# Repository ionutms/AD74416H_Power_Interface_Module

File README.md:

# AD74416H Power Interface Module

## Overview

This repository provides a comprehensive KiCad design for a power and interface module tailored for the Analog Devices AD74416H. This module is designed to supply the necessary power rails and handle digital communications, making it an essential companion for projects utilizing the [Minimal_AD74416H](https://github.com/ionutms/Minimal_AD74416H) board or other AD74416H-based systems.

## Disclaimer

> [!NOTE]
> This project is provided "as is" and without any warranty, express or implied. For more details, please see the [LICENSE](LICENSE) file.

## About the Module

The AD74416H Power Interface Module is engineered to simplify the integration of the AD74416H by providing a stable and reliable power source and a straightforward digital interface. It takes a single power input and generates all the required voltage levels for the AD74416H and its peripherals.

Key features of this module include:

- **Power Supply Generation:** Onboard regulators to generate the necessary positive and negative supply rails for the AD74416H.
- **Digital Interface:** Provides a clear and accessible interface for SPI communication and other digital signals.
- **Modular Design:** Designed to seamlessly connect with the Minimal_AD74416H board.
- **User-Friendly Connectors:** Equipped with standard connectors for easy integration into larger systems.

## Project Structure

```
ad74416h_power_interface_module/
├── ad74416h_power_interface_module.kicad_pro               # Project configuration file
├── ad74416h_power_interface_module.kicad_sch               # Main schematic file
├── ad74416h_power_interface_module.kicad_pcb               # PCB layout file
├── fp-lib-table                                            # Footprint library table
├── sym-lib-table                                           # Symbol library table
├── docs/                                                   # Documentation files
│   ├── bom/                                                # Bill of Materials
│   │   └── ad74416h_power_interface_module_ibom.html       # Interactive BOM file
│   ├── pictures/                                           # Images and photos
│   │   ├── 1_ad74416h_power_interface_module_side.png      # Side view of PCB
│   │   ├── 2_ad74416h_power_interface_module_top.png       # Top view of PCB
│   │   └── 3_ad74416h_power_interface_module_bottom.png    # Bottom view of PCB
│   └── schematics/                                         # Schematic PDF exports
│       └── ad74416h_power_interface_module_schematics.pdf  # Complete schematics PDF
└── KiCAD_Symbols_Generator/                                # Submodule for symbol generation from CSV data
```

## Project Features

This design provides a robust power and interface solution for the AD74416H with:

-   Efficient power conversion and regulation
-   Clear separation of analog and digital grounds
-   Easy-to-use connectors for power and data
-   A compact and modular PCB design

## Getting Started

### Prerequisites

-   [KiCad EDA](https://www.kicad.org/) version 9.0 or later installed on your system
-   Git (for cloning the repository and submodule management)

### Opening the Project

1.  **Clone the repository** (including submodules):
    ```bash
    git clone --recursive https://github.com/ionutms/AD74416H_Power_Interface_Module.git
    ```

    If you've already cloned the repository without submodules, initialize them with:
    ```bash
    git submodule init
    git submodule update
    ```

2.  **Open the project in KiCad**:
    -   Launch KiCad
    -   Click "Open Existing Project"
    -   Navigate to the cloned repository folder
    -   Select the `ad74416h_power_interface_module.kicad_pro` file

3.  **Explore the design**:
    -   Open the schematic editor to view the circuit design
    -   Open the PCB editor to view the board layout
    -   Review the symbol and footprint libraries used in the design

### Project Files

-   **Main schematic**: `ad74416h_power_interface_module.kicad_sch` - Contains the primary circuit design for the power supply and digital interface.
-   **PCB layout**: `ad74416h_power_interface_module.kicad_pcb` - Physical board design file.
-   **Project configuration**: `ad74416h_power_interface_module.kicad_pro` - KiCad project settings.

## Dependencies

This project has the following dependencies:

### 1. KiCAD Symbols Generator

This repository uses [KiCAD_Symbols_Generator](https://github.com/ionutms/KiCAD_Symbols_Generator) as a submodule for custom symbol generation.

To initialize the submodule after cloning this repository:

```bash
git submodule update --init --recursive
```

### 2. 3D Models

This project requires the [3D_Models_Vault](https://github.com/ionutms/3D_Models_Vault) repository for 3D models.

#### Setup for KiCAD 9:

1.  Clone the 3D models repository:
    ```bash
    git clone https://github.com/ionutms/3D_Models_Vault.git
    ```

2.  In KiCAD 9, add an environment variable:
    -   Variable name: `KICAD9_3D_MODELS_VAULT`
    -   Variable value: Full path to where you cloned the 3D_Models_Vault repository

## Usage

After setting up the dependencies, open the project in KiCad 9 to access all features including the 3D models. This module can be used to power and communicate with the [Minimal_AD74416H](https://github.com/ionutms/Minimal_AD74416H) board.

## Symbol Generator Submodule

This project includes the KiCAD_Symbols_Generator as a submodule, which provides tools for generating KiCad symbols from CSV data files. For more information on using this tool, see the [KiCAD_Symbols_Generator documentation](ad74416h_power_interface_module/KiCAD_Symbols_Generator/README.md).

## Documentation

The `docs` folder contains:
-   Schematic PDF exports
-   Images and photos of the design

## Visuals

The following images showcase the PCB design from different perspectives:

*Top View of the PCB*

*Side View of the PCB*

*Bottom View of the PCB*

## License

This project is licensed under the MIT License - see the [LICENSE](LICENSE) file for details.

## References

-   [AD74416H Datasheet](https://www.analog.com/media/en/technical-documentation/data-sheets/ad74416h.pdf)
-   [KiCad EDA](https://www.kicad.org/)

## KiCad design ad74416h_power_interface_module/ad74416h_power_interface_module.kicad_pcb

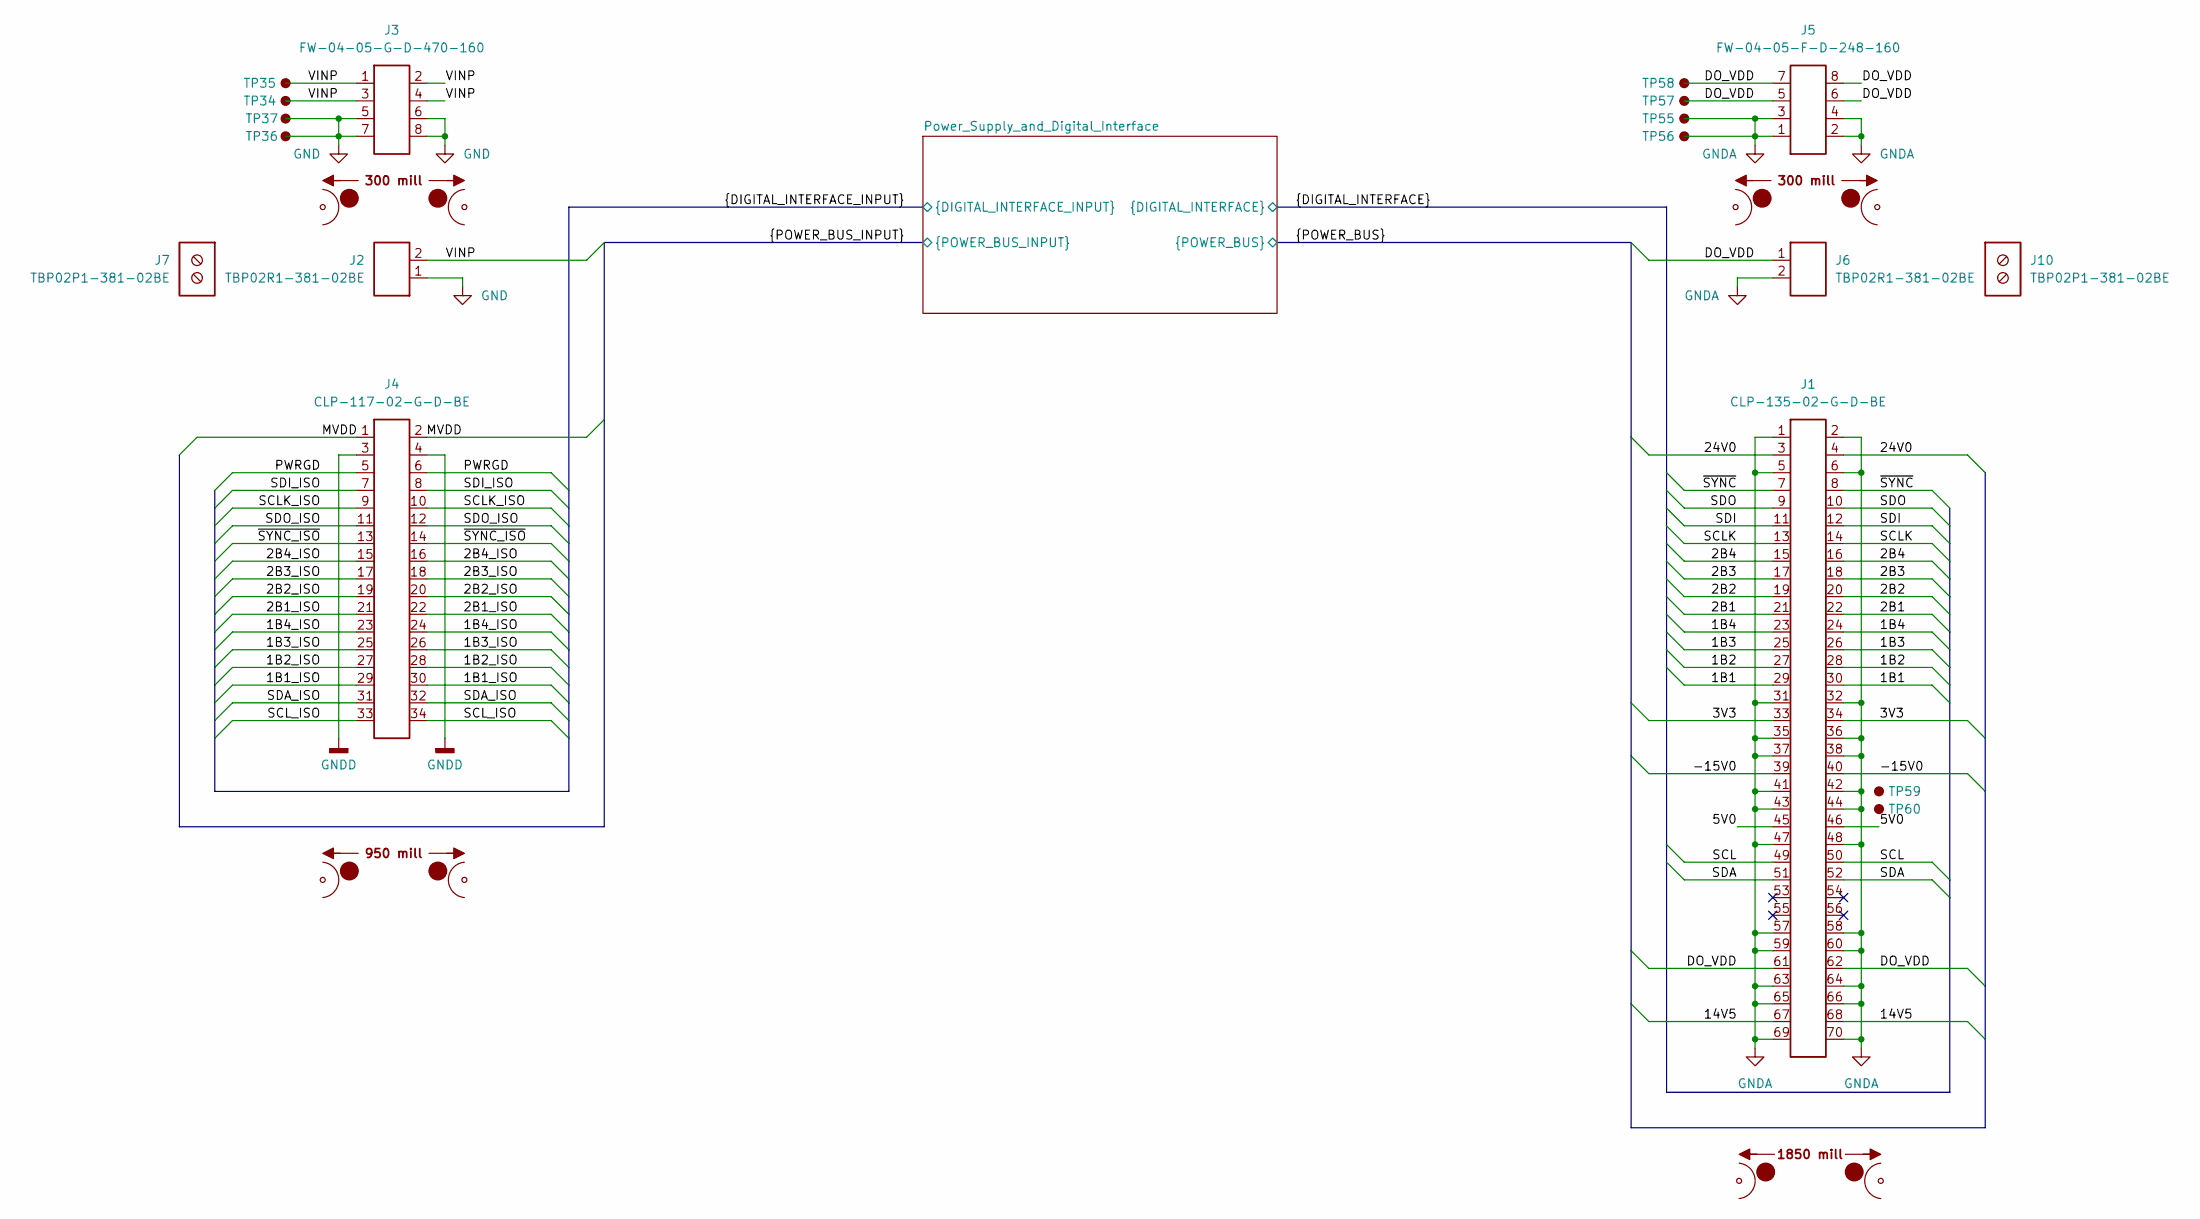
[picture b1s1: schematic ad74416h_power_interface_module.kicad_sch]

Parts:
J1: CLP-135-02-G-D-BE; Current Rating (A) 5.2; Voltage Rating (V) 300; MPN CLP-135-02-G-D-BE
J2, J6: TBP02R1-381-02BE; Current Rating (A) 8.0; Voltage Rating (V) 300; MPN TBP02R1-381-02BE
J3: FW-04-05-G-D-470-160; Current Rating (A) 5.2; Voltage Rating (V) 300; MPN FW-04-05-G-D-470-160
J4: CLP-117-02-G-D-BE; Current Rating (A) 5.2; Voltage Rating (V) 300; MPN CLP-117-02-G-D-BE
J5: FW-04-05-F-D-248-160; Current Rating (A) 5.2; Voltage Rating (V) 300; MPN FW-04-05-F-D-248-160
J7, J10: TBP02P1-381-02BE; Current Rating (A) 8.0; Voltage Rating (V) 300; MPN TBP02P1-381-02BE
MB1: mouse-bite-50mil-1850mil
MB2, MB4: mouse-bite-50mil-300mil
MB3: mouse-bite-50mil-950mil
TP34, TP35, TP36, TP37, TP55, TP56, TP57, TP58, TP59, TP60: TestPoint; TestPoint_THTPad_Castelated

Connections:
/1B1: J1.29, J1.30; also elsewhere on the board
/1B1_ISO: J4.29, J4.30; also elsewhere on the board
/1B2: J1.27, J1.28; also elsewhere on the board
/1B2_ISO: J4.27, J4.28; also elsewhere on the board
/1B3: J1.25, J1.26; also elsewhere on the board
/1B3_ISO: J4.25, J4.26; also elsewhere on the board
/1B4: J1.23, J1.24; also elsewhere on the board
/1B4_ISO: J4.23, J4.24; also elsewhere on the board
/2B1: J1.21, J1.22; also elsewhere on the board
/2B1_ISO: J4.21, J4.22; also elsewhere on the board
/2B2: J1.19, J1.20; also elsewhere on the board
/2B2_ISO: J4.19, J4.20; also elsewhere on the board
/2B3: J1.17, J1.18; also elsewhere on the board
/2B3_ISO: J4.17, J4.18; also elsewhere on the board
/2B4: J1.15, J1.16; also elsewhere on the board
/2B4_ISO: J4.15, J4.16; also elsewhere on the board
/3V3: J1.33, J1.34; also elsewhere on the board
/5V0: J1.45, J1.46; also elsewhere on the board
/14V5: J1.67, J1.68; also elsewhere on the board
/24V0: J1.3, J1.4; also elsewhere on the board
/-15V0: J1.39, J1.40; also elsewhere on the board
/DO_VDD: J1.61, J1.62, J5.5, J5.6, J5.7, J5.8, J6.1, TP57.1, TP58.1; also elsewhere on the board
/MVDD: J4.1, J4.2; also elsewhere on the board
/PWRGD: J4.5, J4.6; also elsewhere on the board
/SCL: J1.49, J1.50; also elsewhere on the board
/SCLK: J1.13, J1.14; also elsewhere on the board
/SCLK_ISO: J4.9, J4.10; also elsewhere on the board
/SCL_ISO: J4.33, J4.34; also elsewhere on the board
/SDA: J1.51, J1.52; also elsewhere on the board
/SDA_ISO: J4.31, J4.32; also elsewhere on the board
/SDI: J1.11, J1.12; also elsewhere on the board
/SDI_ISO: J4.7, J4.8; also elsewhere on the board
/SDO: J1.9, J1.10; also elsewhere on the board
/SDO_ISO: J4.11, J4.12; also elsewhere on the board
/VINP: J2.2, J3.1, J3.2, J3.3, J3.4, TP34.1, TP35.1; also elsewhere on the board
/~SYNC_ISO: J4.13, J4.14; also elsewhere on the board
/~SYNC: J1.7, J1.8; also elsewhere on the board
GND: J2.1, J3.5, J3.6, J3.7, J3.8, TP36.1, TP37.1; also elsewhere on the board
GNDA: J1.1, J1.2, J1.5, J1.6, J1.31, J1.32, J1.35, J1.36, J1.37, J1.38, J1.41, J1.42, J1.43, J1.44, J1.47, J1.48, J1.57, J1.58, J1.59, J1.60, J1.63, J1.64, J1.65, J1.66, J1.69, J1.70, J5.1, J5.2, J5.3, J5.4, J6.2, TP55.1, TP56.1; also elsewhere on the board
GNDD: J4.3, J4.4; also elsewhere on the board

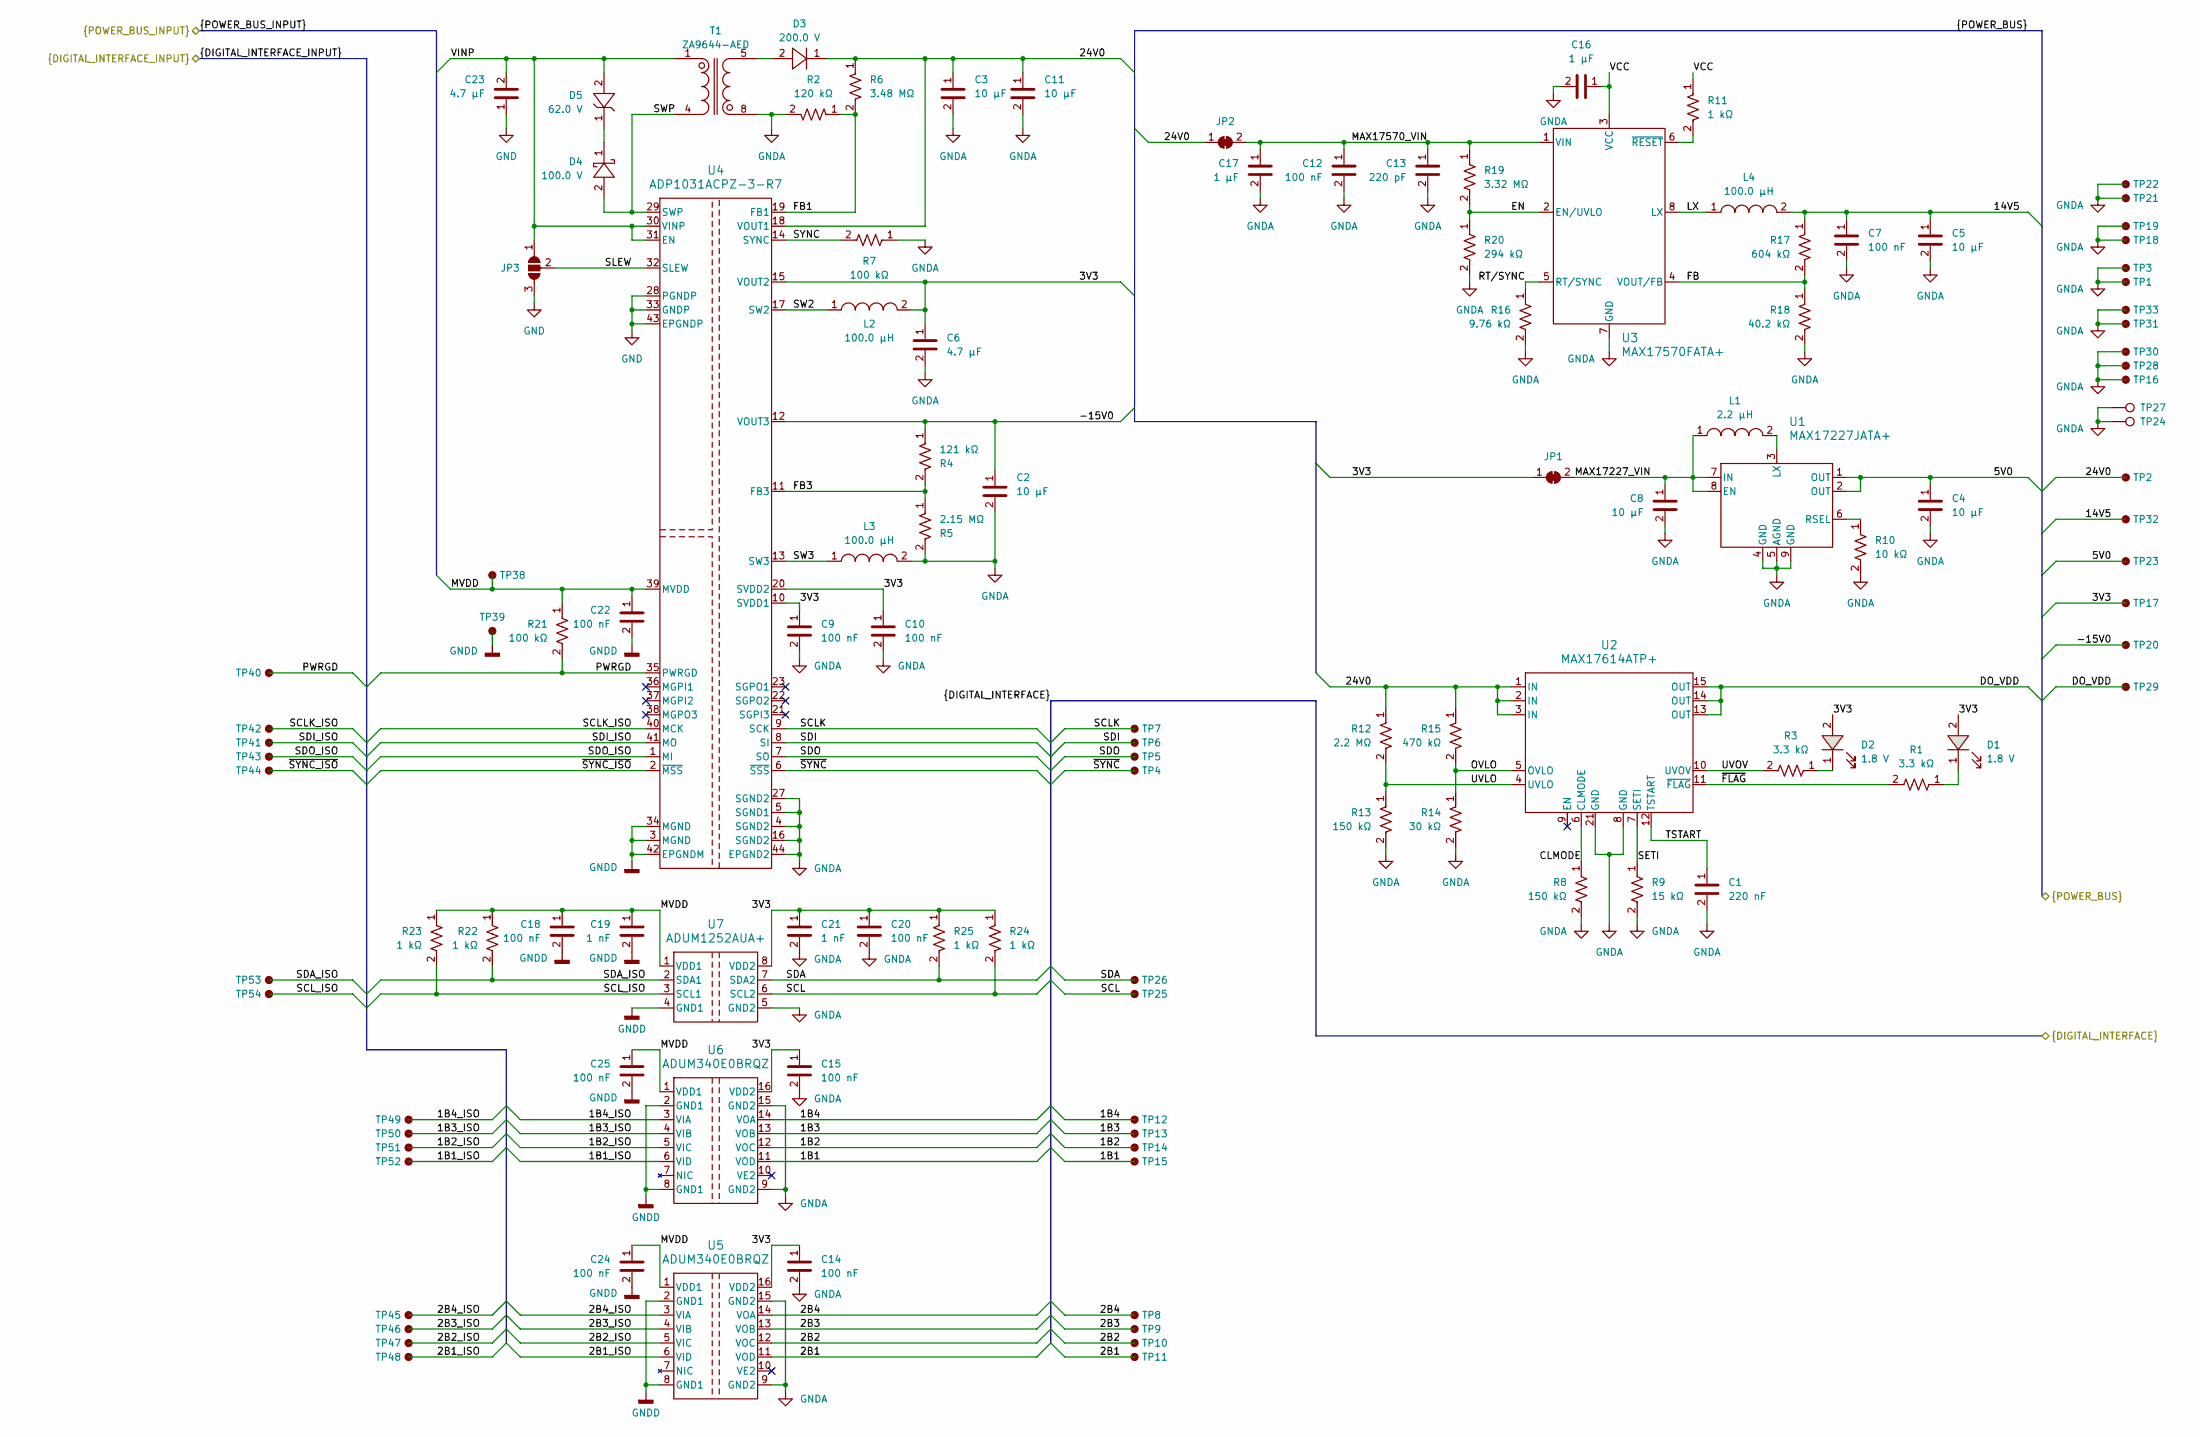
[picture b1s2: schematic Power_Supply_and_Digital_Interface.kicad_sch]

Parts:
C1: 220 nF; C_0402_1005Metric; Tolerance 10%; Voltage Rating 16V; MPN KGM05AR71C224KH
C2, C3, C11: 10 µF; C_1206_3216Metric; Voltage Rating DC 50 VDC; Tolerance 10%; MPN CL31B106KBHNNN#
C4, C8: 10 µF; C_0603_1608Metric; Tolerance 20%; Voltage Rating 16V; MPN C1608X5R1C106M080AB
C5: 10 µF; C_1206_3216Metric; Tolerance 10%; Voltage Rating 50V; MPN CL31B106KBHNNN#
C6: 4.7 µF; C_0603_1608Metric; Voltage Rating DC 10 VDC; Tolerance 10%; MPN C1608X7S1A475K080AC
C7, C12: 100 nF; C_0603_1608Metric; Tolerance 10%; Voltage Rating 100V; MPN C1608X7S2A104K080AB
C9, C10, C14, C15, C18, C20, C22, C24, C25: 100 nF; C_0402_1005Metric; Voltage Rating DC 50 VDC; Tolerance 10%; MPN GCM155R71H104KE02D
C13: 220 pF; C_0402_1005Metric; Tolerance 5%; Voltage Rating 100V; MPN CGA2B2NP02A221J050BA
C16: 1 µF; C_0402_1005Metric; Tolerance 10%; Voltage Rating 16V; MPN C1005X6S1C105K050BC
C17: 1 µF; C_0805_2012Metric; Tolerance 10%; Voltage Rating 100V; MPN GRJ21BC72A105KE11L
C19, C21: 1 nF; C_0402_1005Metric; Tolerance 10%; Voltage Rating 50V; MPN GCM155R71H102KA37D
C23: 4.7 µF; C_1210_200_3225Metric; Tolerance 10%; Voltage Rating 100V; MPN GCM32DC72A475KE02K
D1, D2: 1.8 V; LED_RED_0402_1005Metric; MPN APHHS1005LSECK/J3-PF
D3: 200.0 V; SOD_123F; MPN US1DWF
D4: 100.0 V; PowerDI_123; MPN DFLS1200-7
D5: 62.0 V; SOD_123; MPN MMSZ5265BT1G
JP1, JP2: SolderJumper_2_Bridged; SolderJumper-2_P1.3mm_Bridged_RoundedPad1.0x1.5mm
JP3: SolderJumper_3_Open; SolderJumper-3_P1.3mm_Open_RoundedPad1.0x1.5mm_NumberLabels
L1: 2.2 µH; 74479276; Tolerance ±20%; MPN 74479276222
L2, L3: 100.0 µH; XFL3012; Tolerance ±20%; MPN XFL3012-104ME
L4: 100.0 µH; 74404032; Tolerance ±20%; MPN 74404032101
R1, R3: 3.3 kΩ; R_0402_1005Metric; Tolerance 1%; Voltage Rating 50V; MPN ERJ-2RKF3301X
R2: 120 kΩ; R_0402_1005Metric; Tolerance 1%; Voltage Rating 50V; MPN ERJ-2RKF1203X
R4: 121 kΩ; R_0402_1005Metric; Tolerance 1%; Voltage Rating 50V; MPN ERJ-2RKF1213X
R5: 2.15 MΩ; R_0402_1005Metric; Tolerance 1%; Voltage Rating 50V; MPN RC0402FR-072M15L
R6: 3.48 MΩ; R_0402_1005Metric; Tolerance 1%; Voltage Rating 50V; MPN RC0402FR-073M48L
R7, R21: 100 kΩ; R_0402_1005Metric; Voltage Rating 50V; Tolerance 5%; MPN ERJ-2GEJ104X
R8: 150 kΩ; R_0402_1005Metric; Tolerance 5%; Voltage Rating 50V; MPN ERJ-2GEJ154X
R9: 15 kΩ; R_0402_1005Metric; Tolerance 1%; Voltage Rating 50V; MPN ERJ-2RKF1502X
R10: 10 kΩ; R_0402_1005Metric; Voltage Rating 50V; Tolerance 1%; MPN ERJ-2RKF1002X
R11, R22, R23, R24, R25: 1 kΩ; R_0402_1005Metric; Tolerance 1%; Voltage Rating 50V; MPN ERJ-2RKF1001X
R12: 2.2 MΩ; R_0402_1005Metric; Tolerance 1%; Voltage Rating 50V; MPN RC0402FR-072M2L
R13: 150 kΩ; R_0402_1005Metric; Tolerance 1%; Voltage Rating 50V; MPN ERJ-2RKF1503X
R14: 30 kΩ; R_0402_1005Metric; Tolerance 1%; Voltage Rating 50V; MPN ERJ-2RKF3002X
R15: 470 kΩ; R_0402_1005Metric; Tolerance 1%; Voltage Rating 50V; MPN RC0402FR-07470KL
R16: 9.76 kΩ; R_0402_1005Metric; Tolerance 1%; Voltage Rating 50V; MPN ERJ-2RKF9761X
R17: 604 kΩ; R_0402_1005Metric; Tolerance 1%; Voltage Rating 50V; MPN ERJ-2RKF6043X
R18: 40.2 kΩ; R_0402_1005Metric; Tolerance 1%; Voltage Rating 50V; MPN ERJ-2RKF4022X
R19: 3.32 MΩ; R_0402_1005Metric; Tolerance 1%; Voltage Rating 50V; MPN RC0402FR-073M32L
R20: 294 kΩ; R_0402_1005Metric; Tolerance 1%; Voltage Rating 50V; MPN ERJ-2RKF2943X
T1: ZA9644-AED; ZA9644; Tolerance ±10%; MPN ZA9644-AED
TP1, TP2, TP3, TP4, TP5, TP6, TP7, TP8, TP9, TP10, TP11, TP12, TP13, TP14, TP15, TP16, TP17, TP18, TP19, TP20, TP21, TP22, TP23, TP24, TP25, TP26, TP27, TP28, TP29, TP30, TP31, TP32, TP33, TP38, TP39, TP40, TP41, TP42, TP43, TP44, TP45, TP46, TP47, TP48, TP49, TP50, TP51, TP52, TP53, TP54: TestPoint; TestPoint_THTPad_Castelated
U1: MAX17227JATA+; 21-0168_T822&plus_3C_ADI; MPN MAX17227JATA+
U2: MAX17614ATP+; 21-100172_T2044&plus_4C_MXM_ADI; MPN MAX17614ATP+
U3: MAX17570FATA+; 21-100514_T822C&plus_6C_ADI; MPN MAX17570FATA+
U4: ADP1031ACPZ-3-R7; CP-41-1_ADI; MPN ADP1031ACPZ-3-R7
U5, U6: ADUM340E0BRQZ; RQ-16_ADI; MPN ADUM340E0BRQZ
U7: ADUM1252AUA+; 21-0036_ADI; MPN ADUM1252AUA+

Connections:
/1B1: TP15.1, U6.11 (VOD); also elsewhere on the board
/1B1_ISO: TP52.1, U6.6 (VID); also elsewhere on the board
/1B2: TP14.1, U6.12 (VOC); also elsewhere on the board
/1B2_ISO: TP51.1, U6.5 (VIC); also elsewhere on the board
/1B3: TP13.1, U6.13 (VOB); also elsewhere on the board
/1B3_ISO: TP50.1, U6.4 (VIB); also elsewhere on the board
/1B4: TP12.1, U6.14 (VOA); also elsewhere on the board
/1B4_ISO: TP49.1, U6.3 (VIA); also elsewhere on the board
/2B1: TP11.1, U5.11 (VOD); also elsewhere on the board
/2B1_ISO: TP48.1, U5.6 (VID); also elsewhere on the board
/2B2: TP10.1, U5.12 (VOC); also elsewhere on the board
/2B2_ISO: TP47.1, U5.5 (VIC); also elsewhere on the board
/2B3: TP9.1, U5.13 (VOB); also elsewhere on the board
/2B3_ISO: TP46.1, U5.4 (VIB); also elsewhere on the board
/2B4: TP8.1, U5.14 (VOA); also elsewhere on the board
/2B4_ISO: TP45.1, U5.3 (VIA); also elsewhere on the board
/3V3: C6.1, C9.1, C10.1, C14.1, C15.1, C20.1, C21.1, D1.2, D2.2, JP1.1, L2.2, R24.1, R25.1, TP17.1, U4.10 (SVDD1), U4.15 (VOUT2), U4.20 (SVDD2), U5.16 (VDD2), U6.16 (VDD2), U7.8 (VDD2); also elsewhere on the board
/5V0: C4.1, TP23.1, U1.1 (OUT), U1.2 (OUT); also elsewhere on the board
/14V5: C5.1, C7.1, L4.2, R17.1, TP32.1; also elsewhere on the board
/24V0: C3.1, C11.1, D3.1, JP2.1, R6.1, R12.1, R15.1, TP2.1, U2.1 (IN), U2.2 (IN), U2.3 (IN), U4.18 (VOUT1); also elsewhere on the board
/-15V0: C2.1, R4.1, TP20.1, U4.12 (VOUT3); also elsewhere on the board
/DO_VDD: TP29.1, U2.13 (OUT), U2.14 (OUT), U2.15 (OUT); also elsewhere on the board
/MVDD: C18.1, C19.1, C22.1, C24.1, C25.1, R21.1, R22.1, R23.1, TP38.1, U4.39 (MVDD), U5.1 (VDD1), U6.1 (VDD1), U7.1 (VDD1); also elsewhere on the board
/PWRGD: R21.2, TP40.1, U4.35 (PWRGD); also elsewhere on the board
/Power_Supply_and_Digital_Interface/CLMODE: R8.1, U2.6 (CLMODE)
/Power_Supply_and_Digital_Interface/EN: R19.2, R20.1, U3.2 (EN/UVLO)
/Power_Supply_and_Digital_Interface/FB: R17.2, R18.1, U3.4 (VOUT/FB)
/Power_Supply_and_Digital_Interface/FB1: R2.1, R6.2, U4.19 (FB1)
/Power_Supply_and_Digital_Interface/FB3: R4.2, R5.1, U4.11 (FB3)
/Power_Supply_and_Digital_Interface/LX: L4.1, U3.8 (LX)
/Power_Supply_and_Digital_Interface/MAX17227_VIN: C8.1, JP1.2, L1.1, U1.7 (IN), U1.8 (EN)
/Power_Supply_and_Digital_Interface/MAX17570_VIN: C12.1, C13.1, C17.1, JP2.2, R19.1, U3.1 (VIN)
/Power_Supply_and_Digital_Interface/OVLO: R14.1, R15.2, U2.5 (OVLO)
/Power_Supply_and_Digital_Interface/RT/SYNC: R16.1, U3.5 (RT/SYNC)
/Power_Supply_and_Digital_Interface/SETI: R9.1, U2.7 (SETI)
/Power_Supply_and_Digital_Interface/SLEW: JP3.2 (C), U4.32 (SLEW)
/Power_Supply_and_Digital_Interface/SW2: L2.1, U4.17 (SW2)
/Power_Supply_and_Digital_Interface/SW3: L3.1, U4.13 (SW3)
/Power_Supply_and_Digital_Interface/SWP: D4.2, T1.4, U4.29 (SWP)
/Power_Supply_and_Digital_Interface/SYNC: R7.2, U4.14 (SYNC)
/Power_Supply_and_Digital_Interface/TSTART: C1.1, U2.12 (TSTART)
/Power_Supply_and_Digital_Interface/UVLO: R12.2, R13.1, U2.4 (UVLO)
/Power_Supply_and_Digital_Interface/UVOV: R3.2, U2.10 (UVOV)
/Power_Supply_and_Digital_Interface/VCC: C16.1, R11.1, U3.3 (VCC)
/Power_Supply_and_Digital_Interface/~FLAG: R1.2, U2.11 (~FLAG)
/SCL: R24.2, TP25.1, U7.6 (SCL2); also elsewhere on the board
/SCLK: TP7.1, U4.9 (SCK); also elsewhere on the board
/SCLK_ISO: TP42.1, U4.40 (MCK); also elsewhere on the board
/SCL_ISO: R23.2, TP54.1, U7.3 (SCL1); also elsewhere on the board
/SDA: R25.2, TP26.1, U7.7 (SDA2); also elsewhere on the board
/SDA_ISO: R22.2, TP53.1, U7.2 (SDA1); also elsewhere on the board
/SDI: TP6.1, U4.8 (SI); also elsewhere on the board
/SDI_ISO: TP41.1, U4.41 (MO); also elsewhere on the board
/SDO: TP5.1, U4.7 (SO); also elsewhere on the board
/SDO_ISO: TP43.1, U4.1 (MI); also elsewhere on the board
/VINP: C23.2, D5.2, JP3.1 (A), T1.1, U4.30 (VINP), U4.31 (EN); also elsewhere on the board
/~SYNC_ISO: TP44.1, U4.2 (~MSS); also elsewhere on the board
/~SYNC: TP4.1, U4.6 (~SSS); also elsewhere on the board
GND: C23.1, JP3.3 (B), U4.28 (PGNDP), U4.33 (GNDP), U4.43 (EPGNDP); also elsewhere on the board
GNDA: C1.2, C2.2, C3.2, C4.2, C5.2, C6.2, C7.2, C8.2, C9.2, C10.2, C11.2, C12.2, C13.2, C14.2, C15.2, C16.2, C17.2, C20.2, C21.2, L3.2, R2.2, R5.2, R7.1, R8.2, R9.2, R10.2, R13.2, R14.2, R16.2, R18.2, R20.2, T1.8, TP1.1, TP3.1, TP16.1, TP18.1, TP19.1, TP21.1, TP22.1, TP24.1, TP27.1, TP28.1, TP30.1, TP31.1, TP33.1, U1.4 (GND), U1.5 (AGND), U1.9 (GND), U2.8 (GND), U2.21 (GND), U3.7 (GND), U4.4 (SGND2), U4.5 (SGND1), U4.16 (SGND2), U4.27 (SGND2), U4.44 (EPGND2), U5.9 (GND2), U5.15 (GND2), U6.9 (GND2), U6.15 (GND2), U7.5 (GND2); also elsewhere on the board
GNDD: C18.2, C19.2, C22.2, C24.2, C25.2, TP39.1, U4.3 (MGND), U4.34 (MGND), U4.42 (EPGNDM), U5.2 (GND1), U5.8 (GND1), U6.2 (GND1), U6.8 (GND1), U7.4 (GND1); also elsewhere on the board
unnamed: D1.1, R1.1
unnamed: D2.1, R3.1
unnamed: D3.2, T1.5
unnamed: D4.1, D5.1
unnamed: L1.2, U1.3 (LX)
unnamed: R10.1, U1.6 (RSEL)
unnamed: R11.2, U3.6 (~RESET)

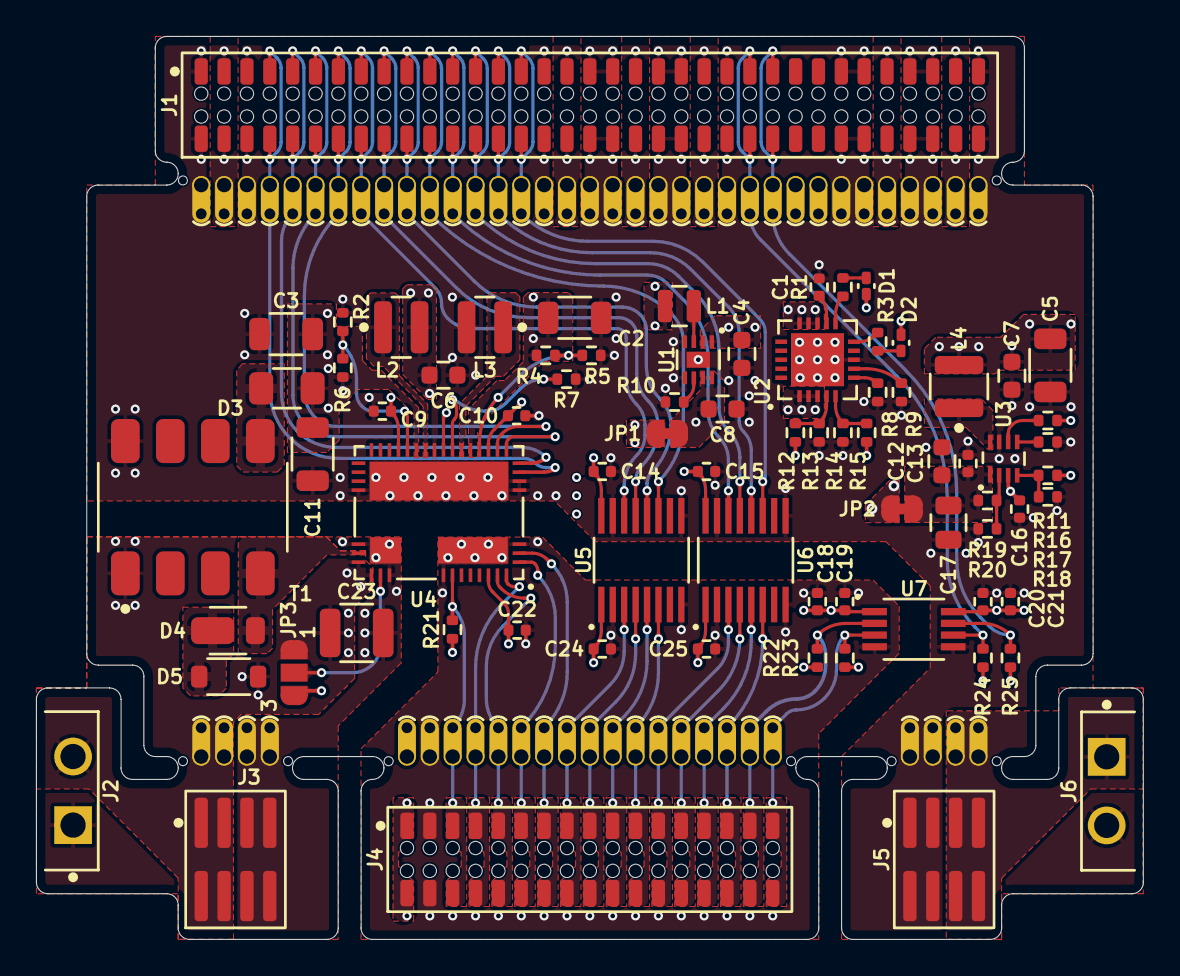
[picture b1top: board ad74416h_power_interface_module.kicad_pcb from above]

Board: 4 copper layers, 61.5 x 50.2 mm, 142 parts (0 on the bottom side), 68 nets.

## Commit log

2025-09-15 Add KiCAD project files and GitHub workflows for AD74416H Power Interface Module
2025-09-15 Update KiCad documentation for ad74416h_power_interface_module (schematics and PCB renders)
2025-09-15 backup
2025-09-16 Update README.md with comprehensive project documentation
2025-10-04 Update KiCad camera zoom factors in configuration
2025-10-04 Update side_view_pan in KiCad configuration
2025-10-04 Update side_view_zoom_factor and side_view_pan in KiCad configuration
2025-10-04 Add new trigger-symbol-check workflow
2025-10-04 Enhance trigger-symbol-check workflow with dynamic path detection
2025-10-04 Add support for left/right views and pan parameters in KiCAD render workflow
2025-10-04 Update workflows to trigger symbol check from generate_kicad_jobs
2025-10-04 Fix duplicate sha parameter in generate_kicad_jobs.yml
2025-10-05 chore: update workflows and kicad config from central repository
2025-10-24 Update PCB design
2025-10-24 Update kicad-config.yml settings
2025-11-01 Add new view configurations to kicad-config.yml
2025-11-02 Update PCB file
2025-11-02 Update project file
